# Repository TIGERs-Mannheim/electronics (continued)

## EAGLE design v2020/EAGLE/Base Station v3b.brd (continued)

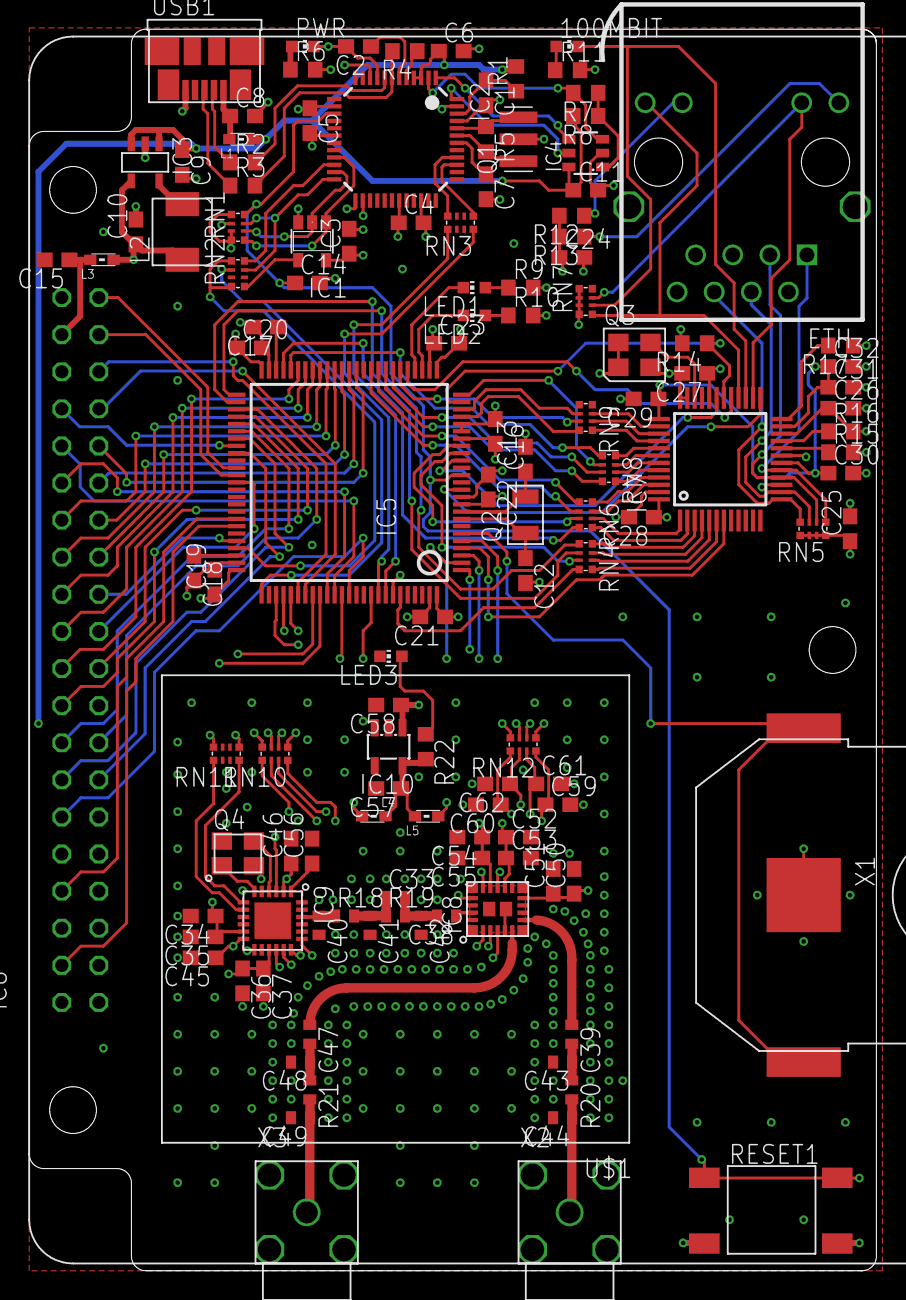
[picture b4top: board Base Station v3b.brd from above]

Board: 4 copper layers, 58.0 x 85.0 mm, 127 parts (0 on the bottom side), 157 nets.

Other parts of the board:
U$1: BMI-S-204-F; SHIELD-32MM

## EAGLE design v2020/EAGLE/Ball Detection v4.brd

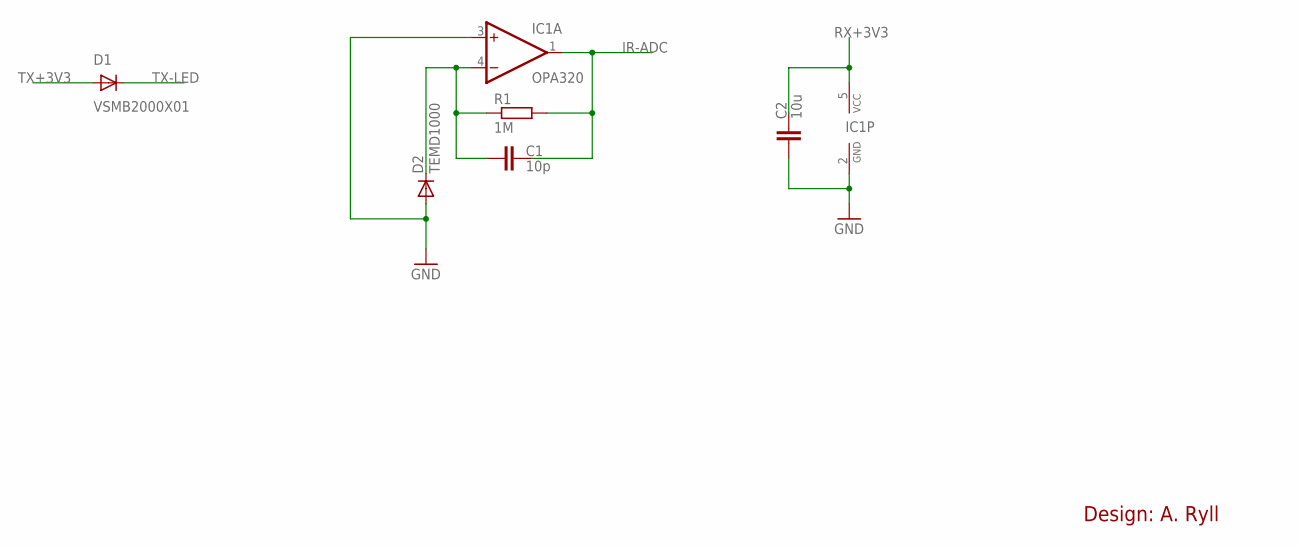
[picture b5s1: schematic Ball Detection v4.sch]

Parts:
C1: 10p; C0603
C2: 10u; C0603
D1: VSMB2000X01; LED-GULLR
D2: TEMD1000; LED-GULLR
IC1: OPA320; SOT23-5
R1: 1M; R0603

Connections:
GND: C2.1, D2.A, IC1.2 (GND), IC1.3 (+IN)
IR-ADC: C1.2, IC1.1 (OUT), R1.2
unnamed: C1.1, D2.C, IC1.4 (-IN), R1.1
RX+3V3: C2.2, IC1.5 (VCC)
TX+3V3: D1.A
TX-LED: D1.C

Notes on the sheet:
Design: A. Ryll

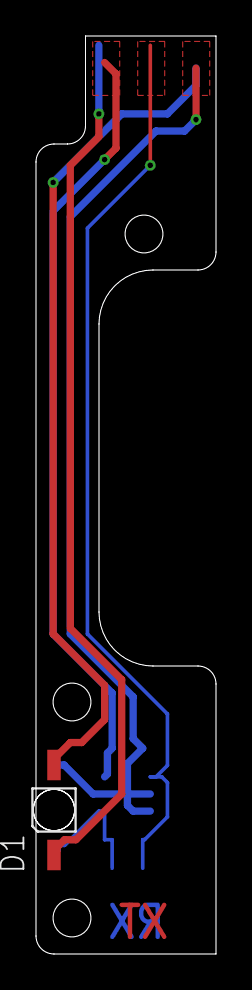
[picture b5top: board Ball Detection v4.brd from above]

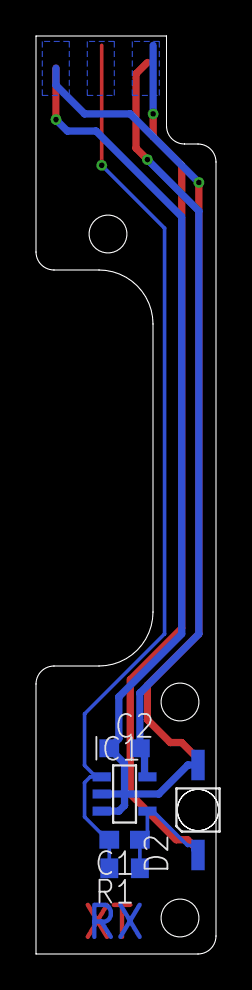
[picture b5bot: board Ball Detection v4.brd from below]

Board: 2 copper layers, 10.0 x 51.0 mm, 6 parts (5 on the bottom side), 4 nets.

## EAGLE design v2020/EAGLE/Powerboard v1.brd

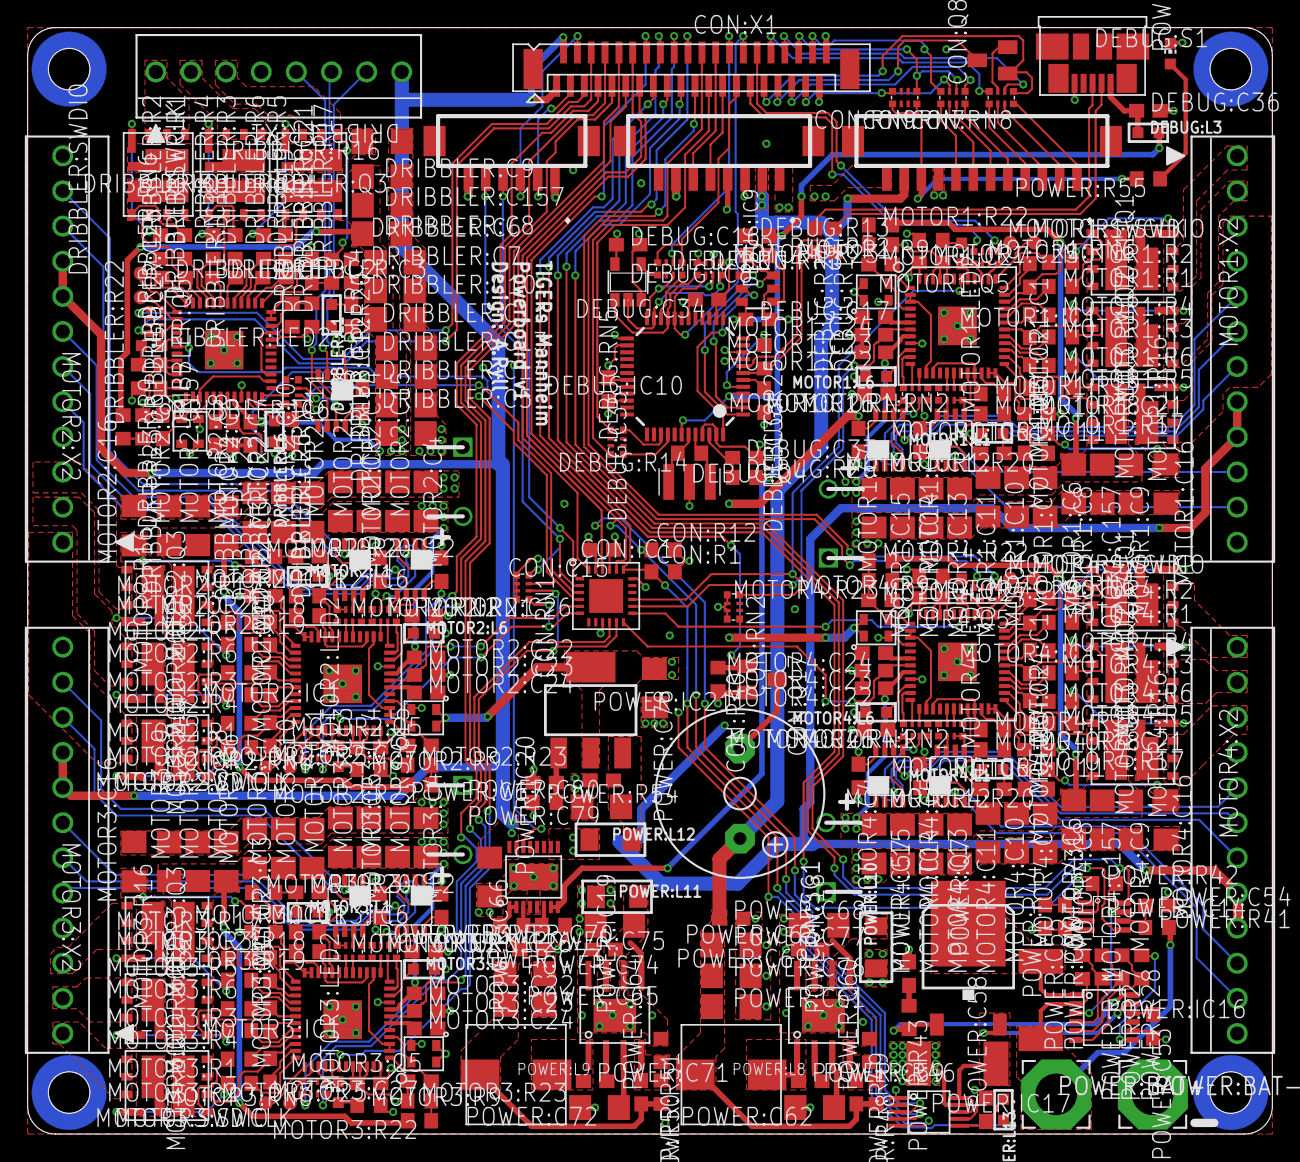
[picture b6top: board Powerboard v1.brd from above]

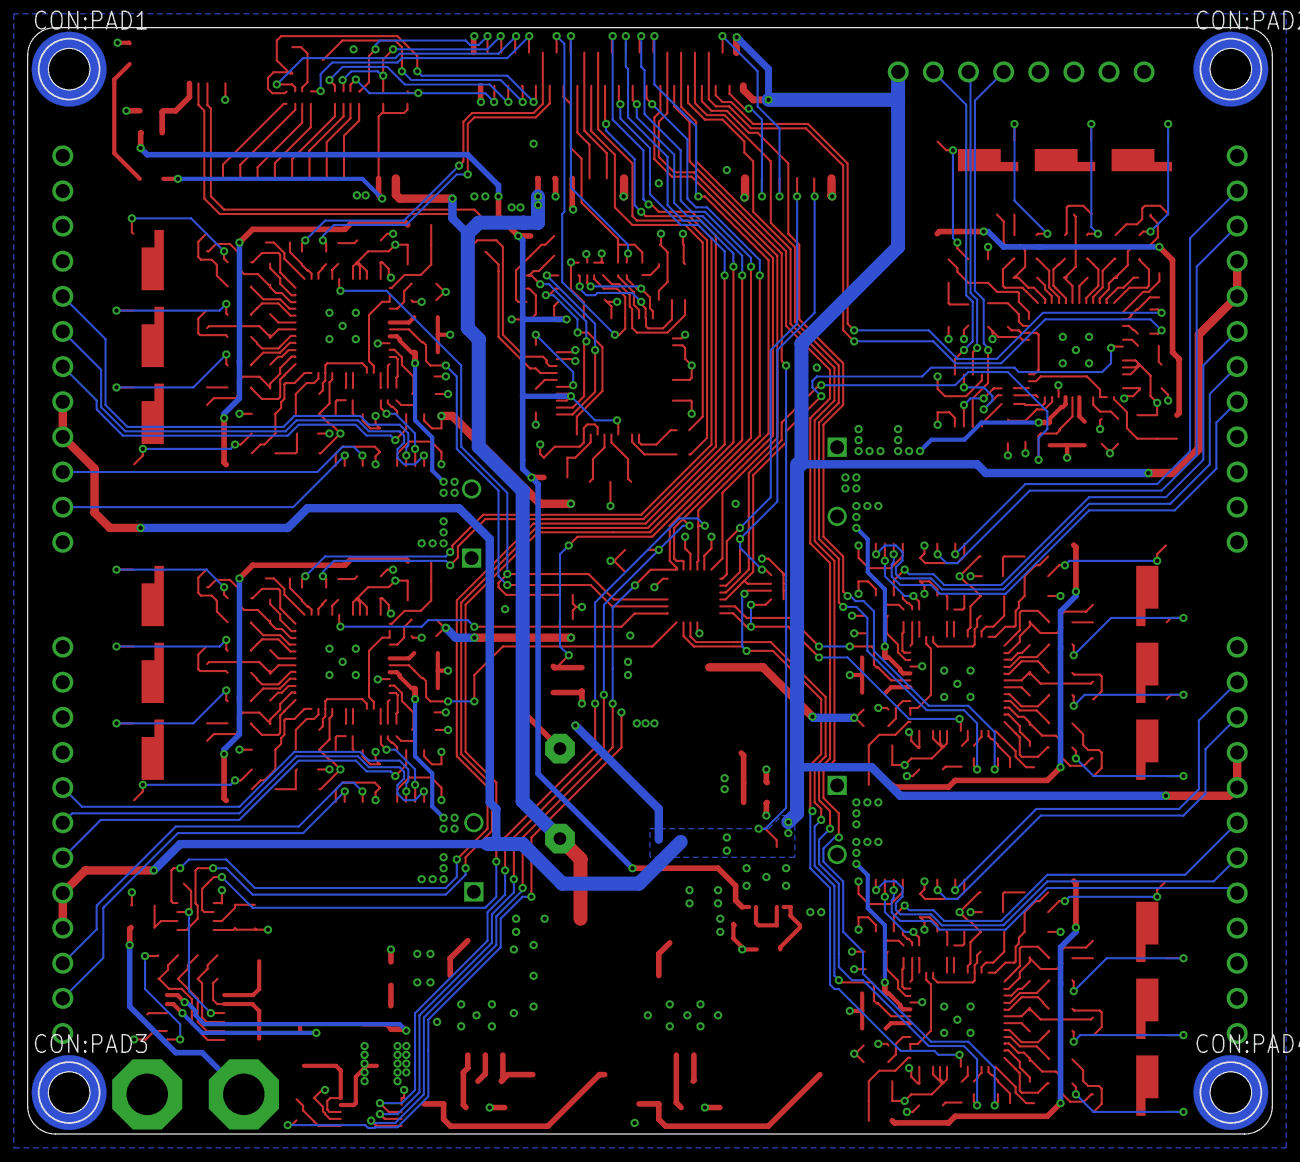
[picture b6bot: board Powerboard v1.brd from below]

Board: 4 copper layers, 90.0 x 80.0 mm, 372 parts (4 on the bottom side), 363 nets.

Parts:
CON:C15: 100n; C0603
CON:EXT: DF13-8P-1.25V; DF13C-8P-1.25V
CON:IC1: TCA9539RTW; WQFN24
CON:IR: DF13-6P-1.25V; DF13C-6P-1.25V
CON:KD: DF13-12P-1.25V; DF13C-12P-1.25V
CON:PAD1, CON:PAD2, CON:PAD3: 5,4/3,0
CON:PAD4: 9774030243R; 5,4/3,0
CON:Q8: BSS84; SOT23
CON:Q17: BSS138; SOT23
CON:R1, CON:R12: 1k33 1%; R0603
CON:R40: 5k6; R0603
CON:RN1, CON:RN2, CON:RN9: 10k; EXB28V
CON:RN7, CON:RN8: 100; EXB28V
CON:SG1: CEM-1212S; F/QMX
CON:X1: 4-1734742-0; TE-4-1734742-0
DEBUG:C16, DEBUG:C17, DEBUG:C34, DEBUG:C35, DEBUG:C36, DEBUG:C37, DEBUG:C38: 100n; C0603
DEBUG:IC8: 74LVC1G125DBV; SOT23-5
DEBUG:IC9: 93C76B; SOT23-6
DEBUG:IC10: FT2232ST; LQFP48-ST
DEBUG:L3: 120R; L0603
DEBUG:Q4: CSTCR6M00G55-R0; CSTCR6M
DEBUG:R12, DEBUG:R26: 1k; R0603
DEBUG:R13: 5k6; R0603
DEBUG:R14: 1M; R0603
DEBUG:R15, DEBUG:R24: 33; R0603
DEBUG:R25: 1k33 1%; R0603
DEBUG:RN3: 10k; EXB28V
DEBUG:RN4, DEBUG:RN5: 100; EXB28V
DEBUG:S1: USB-BU; USB-BMICRO
DRIBBLER:C1, DRIBBLER:C2, DRIBBLER:C3, DRIBBLER:C4, DRIBBLER:C12, DRIBBLER:C23, DRIBBLER:C25, DRIBBLER:C26: 100n; C0603
DRIBBLER:C5, DRIBBLER:C6, DRIBBLER:C7, DRIBBLER:C8, DRIBBLER:C9, DRIBBLER:C10, DRIBBLER:C11, DRIBBLER:C13, DRIBBLER:C14, DRIBBLER:C157: 10u; C1206
DRIBBLER:C21: 47p; C0603
DRIBBLER:C22, DRIBBLER:C24, DRIBBLER:C27: 1u; C0603
DRIBBLER:IC1: STSPIN32F0A; VFQFPN48
DRIBBLER:IC6: SN74LVC3G17DCT; DCT_R-PDSO-G8
DRIBBLER:L1, DRIBBLER:L6: 120R; L0603
DRIBBLER:LED2: gr; CHIP-LED0603
DRIBBLER:Q1, DRIBBLER:Q2, DRIBBLER:Q3: FDMD85100; POWER56_HBRIDGE
DRIBBLER:Q5: KC2016K4.00000C1GE00; OSCI-KC2016
DRIBBLER:R1, DRIBBLER:R2, DRIBBLER:R3, DRIBBLER:R4, DRIBBLER:R5, DRIBBLER:R6: 33; R0603
DRIBBLER:R9: 1k; R0603
DRIBBLER:R16: 0R025; R1206
DRIBBLER:R17, DRIBBLER:R18: 1k33 1%; R0603
DRIBBLER:R19: 7k32 1%; R0603
DRIBBLER:R20: 16k2 1%; R0603
DRIBBLER:R22: 243k 1%; R0603
DRIBBLER:R23: 24k 1%; R0603
DRIBBLER:RN1, DRIBBLER:RN6: 100; EXB28V
DRIBBLER:SWCLK: TPTP10R; TP10R
DRIBBLER:SWDIO: TPTP10R; TP10R
DRIBBLER:X1: 640454-8
MOTOR1:C1, MOTOR1:C2, MOTOR1:C3, MOTOR1:C4, MOTOR1:C5, MOTOR1:C12, MOTOR1:C23, MOTOR1:C25, MOTOR1:C26, MOTOR2:C1, MOTOR2:C2, MOTOR2:C3, MOTOR2:C4, MOTOR2:C5, MOTOR2:C12, MOTOR2:C23, MOTOR2:C25, MOTOR2:C26, MOTOR3:C1, MOTOR3:C2, MOTOR3:C3, MOTOR3:C4, MOTOR3:C5, MOTOR3:C12, MOTOR3:C23, MOTOR3:C25, MOTOR3:C26, MOTOR4:C1, MOTOR4:C2, MOTOR4:C3, MOTOR4:C4, MOTOR4:C5, MOTOR4:C12, MOTOR4:C23, MOTOR4:C25, MOTOR4:C26: 100n; C0603
MOTOR1:C6, MOTOR1:C7, MOTOR1:C8, MOTOR1:C9, MOTOR1:C10, MOTOR1:C11, MOTOR1:C13, MOTOR1:C14, MOTOR1:C15, MOTOR1:C157, MOTOR2:C6, MOTOR2:C7, MOTOR2:C8, MOTOR2:C9, MOTOR2:C10, MOTOR2:C11, MOTOR2:C13, MOTOR2:C14, MOTOR2:C15, MOTOR2:C157, MOTOR3:C6, MOTOR3:C7, MOTOR3:C8, MOTOR3:C9, MOTOR3:C10, MOTOR3:C11, MOTOR3:C13, MOTOR3:C14, MOTOR3:C15, MOTOR3:C157, MOTOR4:C6, MOTOR4:C7, MOTOR4:C8, MOTOR4:C9, MOTOR4:C10, MOTOR4:C11, MOTOR4:C13, MOTOR4:C14, MOTOR4:C15, MOTOR4:C157: 10u; C1206
MOTOR1:C16, MOTOR2:C16, MOTOR3:C16, MOTOR4:C16: 470u; C22-12.5L
MOTOR1:C21, MOTOR2:C21, MOTOR3:C21, MOTOR4:C21: 47p; C0603
MOTOR1:C22, MOTOR1:C24, MOTOR1:C27, MOTOR2:C22, MOTOR2:C24, MOTOR2:C27, MOTOR3:C22, MOTOR3:C24, MOTOR3:C27, MOTOR4:C22, MOTOR4:C24, MOTOR4:C27: 1u; C0603
MOTOR1:IC1, MOTOR2:IC1, MOTOR3:IC1, MOTOR4:IC1: STSPIN32F0A; VFQFPN48
MOTOR1:IC6, MOTOR1:IC11, MOTOR2:IC6, MOTOR2:IC11, MOTOR3:IC6, MOTOR3:IC11, MOTOR4:IC6, MOTOR4:IC11: SN74LVC3G17DCT; DCT_R-PDSO-G8
MOTOR1:L1, MOTOR1:L6, MOTOR2:L1, MOTOR2:L6, MOTOR3:L1, MOTOR3:L6, MOTOR4:L1, MOTOR4:L6: 120R; L0603
MOTOR1:LED2, MOTOR2:LED2, MOTOR3:LED2, MOTOR4:LED2: gr; CHIP-LED0603
MOTOR1:Q1, MOTOR1:Q2, MOTOR1:Q3, MOTOR2:Q1, MOTOR2:Q2, MOTOR2:Q3, MOTOR3:Q1, MOTOR3:Q2, MOTOR3:Q3, MOTOR4:Q1, MOTOR4:Q2, MOTOR4:Q3: FDMD85100; POWER56_HBRIDGE
MOTOR1:Q5, MOTOR2:Q5, MOTOR3:Q5, MOTOR4:Q5: KC2016K4.00000C1GE00; OSCI-KC2016
MOTOR1:R1, MOTOR1:R2, MOTOR1:R3, MOTOR1:R4, MOTOR1:R5, MOTOR1:R6, MOTOR2:R1, MOTOR2:R2, MOTOR2:R3, MOTOR2:R4, MOTOR2:R5, MOTOR2:R6, MOTOR3:R1, MOTOR3:R2, MOTOR3:R3, MOTOR3:R4, MOTOR3:R5, MOTOR3:R6, MOTOR4:R1, MOTOR4:R2, MOTOR4:R3, MOTOR4:R4, MOTOR4:R5, MOTOR4:R6: 33; R0603
MOTOR1:R9, MOTOR2:R9, MOTOR3:R9, MOTOR4:R9: 1k; R0603
MOTOR1:R16, MOTOR2:R16, MOTOR3:R16, MOTOR4:R16: 0R025; R1206
MOTOR1:R17, MOTOR1:R18, MOTOR2:R17, MOTOR2:R18, MOTOR3:R17, MOTOR3:R18, MOTOR4:R17, MOTOR4:R18: 1k33 1%; R0603
MOTOR1:R19, MOTOR2:R19, MOTOR3:R19, MOTOR4:R19: 7k32 1%; R0603
MOTOR1:R20, MOTOR2:R20, MOTOR3:R20, MOTOR4:R20: 16k2 1%; R0603
MOTOR1:R22, MOTOR2:R22, MOTOR3:R22, MOTOR4:R22: 243k 1%; R0603
MOTOR1:R23, MOTOR2:R23, MOTOR3:R23, MOTOR4:R23: 24k 1%; R0603
MOTOR1:RN1, MOTOR1:RN2, MOTOR1:RN6, MOTOR2:RN1, MOTOR2:RN2, MOTOR2:RN6, MOTOR3:RN1, MOTOR3:RN2, MOTOR3:RN6, MOTOR4:RN1, MOTOR4:RN2, MOTOR4:RN6: 100; EXB28V
MOTOR1:SWCLK, MOTOR1:SWDIO, MOTOR2:SWCLK, MOTOR2:SWDIO, MOTOR3:SWCLK, MOTOR3:SWDIO, MOTOR4:SWCLK, MOTOR4:SWDIO: TPTP10R; TP10R
MOTOR1:X2, MOTOR2:X2, MOTOR3:X2, MOTOR4:X2: 1-640454-2
POWER:BAT+: 5,08/3
POWER:BAT-: 5,08/3
POWER:C53, POWER:C54, POWER:C55, POWER:C56, POWER:C58, POWER:C67, POWER:C68, POWER:C69, POWER:C73, POWER:C75, POWER:C80: 100n; C0603
POWER:C57: 10n; C0603
POWER:C59, POWER:C71: 1u; C0603
POWER:C60, POWER:C64: 18p; C0603
POWER:C61, POWER:C65, POWER:C74, POWER:C76, POWER:C77, POWER:C78, POWER:C79: 33u; C1206
POWER:C62, POWER:C63, POWER:C66, POWER:C70, POWER:C72: 10u; C1206
POWER:IC14: LTC2955CTS8-1; SOT23-8
POWER:IC16: LTC4231CMS-2; MSOP-12
POWER:IC17: INA226; DGS_S-PDSO-G10
POWER:IC18, POWER:IC19: LMR23630ADDA; DDA_R-PDSO-G8
POWER:IC20: LTC4415MSE; MSOP-16P
POWER:IC21: LT3080ST; SOT223
POWER:L8, POWER:L9: 7443251600; WE-HCI
POWER:L10, POWER:L11, POWER:L12: 470R; L1206
POWER:L13: 120R; L0603
POWER:LED1: gr; CHIP-LED0603
POWER:Q7: FDD86367; D-PAK_TO252AA
POWER:R11: 5k6; R0603
POWER:R27: 40k2 1%; R0603
POWER:R28: 24k 1%; R0603
POWER:R31, POWER:R42: 1M; R0603
POWER:R41: 7k32 1%; R0603
POWER:R43, POWER:R55: 1k; R0603
POWER:R44: 0R001; R2512
POWER:R46: 0R002; R2512
POWER:R48: 243k 1%; R0603
POWER:R49, POWER:R51, POWER:R52: 22k1 1%; R0603
POWER:R50, POWER:R53: 88k7 1%; R0603
POWER:R54: 330k; R0603

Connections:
5V_USB: DEBUG:C17.1, DEBUG:IC9.6, DEBUG:IC10.3, DEBUG:IC10.4, DEBUG:IC10.42, DEBUG:L3.2, DEBUG:R13.2, DEBUG:R26.2, POWER:IC20.7, POWER:IC20.8
+3V3: CON:C15.1, CON:EXT.P$4, CON:IC1.21, CON:IR.P$1, CON:KD.P$10, CON:R1.2, CON:R12.2, CON:RN9.5, CON:RN9.8, DEBUG:C16.1, DEBUG:C34.1, DEBUG:C35.1, DEBUG:IC8.5, DEBUG:IC10.10, DEBUG:IC10.14, DEBUG:IC10.26, DEBUG:IC10.31, DEBUG:RN3.5, DEBUG:RN3.7, DEBUG:RN3.8, DRIBBLER:C4.1, DRIBBLER:C25.1, DRIBBLER:IC1.9, DRIBBLER:IC1.48, DRIBBLER:IC6.8, DRIBBLER:L1.2, DRIBBLER:L6.2, DRIBBLER:Q5.1, DRIBBLER:Q5.4, DRIBBLER:R9.2, MOTOR1:C4.1, MOTOR1:C5.1, MOTOR1:C25.1, MOTOR1:IC1.9, MOTOR1:IC1.48, MOTOR1:IC6.8, MOTOR1:IC11.8, MOTOR1:L1.2, MOTOR1:L6.2, MOTOR1:Q5.1, MOTOR1:Q5.4, MOTOR1:R9.2, MOTOR2:C4.1, MOTOR2:C5.1, MOTOR2:C25.1, MOTOR2:IC1.9, MOTOR2:IC1.48, MOTOR2:IC6.8, MOTOR2:IC11.8, MOTOR2:L1.2, MOTOR2:L6.2, MOTOR2:Q5.1, MOTOR2:Q5.4, MOTOR2:R9.2, MOTOR3:C4.1, MOTOR3:C5.1, MOTOR3:C25.1, MOTOR3:IC1.9, MOTOR3:IC1.48, MOTOR3:IC6.8, MOTOR3:IC11.8, MOTOR3:L1.2, MOTOR3:L6.2, MOTOR3:Q5.1, MOTOR3:Q5.4, MOTOR3:R9.2, MOTOR4:C4.1, MOTOR4:C5.1, MOTOR4:C25.1, MOTOR4:IC1.9, MOTOR4:IC1.48, MOTOR4:IC6.8, MOTOR4:IC11.8, MOTOR4:L1.2, MOTOR4:L6.2, MOTOR4:Q5.1, MOTOR4:Q5.4, MOTOR4:R9.2, POWER:C78.1, POWER:IC21.2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
+5V: CON:EXT.P$3, CON:X1.1, CON:X1.2, DRIBBLER:X1.8, MOTOR1:X2.8, MOTOR1:X2.9, MOTOR2:X2.8, MOTOR2:X2.9, MOTOR3:X2.8, MOTOR3:X2.9, MOTOR4:X2.8, MOTOR4:X2.9, POWER:C66.1, POWER:IC20.9, POWER:IC20.10, POWER:IC20.15, POWER:IC20.16, POWER:L12.1
+12V: CON:EXT.P$2, CON:KD.P$11, CON:SG1.+, POWER:C60.1, POWER:C61.1, POWER:C68.1, POWER:C76.1, POWER:C77.1, POWER:L8.1, POWER:R48.2
BOOT0: CON:IC1.15, CON:RN2.8, MOTOR1:IC1.42
BOOT1: CON:IC1.6, CON:RN1.5, MOTOR2:IC1.42
BOOT2: CON:IC1.11, CON:RN1.6, MOTOR3:IC1.42
BOOT3: CON:IC1.13, CON:RN2.5, MOTOR4:IC1.42
BOOT4: CON:IC1.4, CON:RN1.7, DRIBBLER:IC1.42
BOOT5: CON:IC1.2, CON:IR.P$5, CON:RN1.8
BTN: CON:X1.18, POWER:IC14.5
CON:BUZZER: CON:Q17.1, CON:R40.1, CON:X1.16
CON:KICK-CHG: CON:RN7.1, CON:X1.35
CON:KICK-CLK: CON:RN8.2, CON:X1.34
CON:KICK-CS: CON:Q8.1, CON:RN8.1, CON:X1.31
CON:KICK-DIS1: CON:RN7.2, CON:RN9.1, CON:X1.36
CON:KICK-DIS2: CON:RN7.3, CON:RN9.4, CON:X1.37
CON:KICK-ERR: CON:RN7.4, CON:X1.38
CON:KICK-MISO: CON:Q8.3, CON:X1.33
CON:KICK-MOSI: CON:RN8.4, CON:X1.32
CON:N$1: CON:Q17.3, CON:SG1.-
CON:N$2: CON:Q8.2, CON:RN8.3
CON:N$3: CON:KD.P$1, CON:RN8.8
CON:N$4: CON:KD.P$2, CON:RN8.7
CON:N$5: CON:KD.P$3, CON:RN8.6
CON:N$6: CON:KD.P$4, CON:RN8.5
CON:N$7: CON:KD.P$5, CON:RN7.8
CON:N$8: CON:KD.P$6, CON:RN7.7
CON:N$9: CON:KD.P$7, CON:RN7.6
CON:N$10: CON:KD.P$8, CON:RN7.5
CON:SMB-RST: CON:IC1.24, CON:X1.12
DEBUG:EECS: DEBUG:IC9.5, DEBUG:IC10.48
DEBUG:EEDATA: DEBUG:IC9.3, DEBUG:IC10.2, DEBUG:R12.1
DEBUG:EESK: DEBUG:IC9.4, DEBUG:IC10.1
DEBUG:N$61: DEBUG:IC9.1, DEBUG:R12.2, DEBUG:R13.1
DEBUG:N$62: DEBUG:IC10.43, DEBUG:Q4.1, DEBUG:R14.2
DEBUG:N$63: DEBUG:IC10.40, DEBUG:RN5.1
DEBUG:N$64: DEBUG:IC10.44, DEBUG:Q4.3, DEBUG:R14.1
DEBUG:N$71: DEBUG:IC10.8, DEBUG:R15.2
DEBUG:N$72: DEBUG:IC10.7, DEBUG:R24.2, DEBUG:R25.2
DEBUG:N$85: DEBUG:R15.1, DEBUG:S1.2
DEBUG:N$86: DEBUG:R24.1, DEBUG:S1.3
DEBUG:N$87: DEBUG:IC10.5, DEBUG:R25.1
DEBUG:N$88: DEBUG:C37.1, DEBUG:IC10.46, DEBUG:R26.1
DEBUG:N$89: DEBUG:IC10.24, DEBUG:RN3.3, DEBUG:RN4.3
DEBUG:N$90: DEBUG:C36.1, DEBUG:L3.1, DEBUG:S1.1
DEBUG:N$91: DEBUG:IC8.2, DEBUG:IC10.23, DEBUG:RN3.4
DEBUG:N$92: DEBUG:IC8.4, DEBUG:RN4.1
DEBUG:N$93: DEBUG:IC10.39, DEBUG:RN5.4
DEBUG:N$94: DEBUG:IC10.22, DEBUG:RN4.4
DEBUG:N$95: DEBUG:IC8.1, DEBUG:IC10.21, DEBUG:RN3.1
DEBUG:N$96: DEBUG:C38.1, DEBUG:IC10.6
DRIBBLER:M1-CUR: DRIBBLER:IC1.15, DRIBBLER:IC1.21, DRIBBLER:R19.1
DRIBBLER:M1-H1: DRIBBLER:IC6.3, DRIBBLER:X1.6
DRIBBLER:M1-H2: DRIBBLER:IC6.6, DRIBBLER:X1.5
DRIBBLER:M1-H3: DRIBBLER:IC6.1, DRIBBLER:X1.7
DRIBBLER:M1-LED: DRIBBLER:IC1.41, DRIBBLER:LED2.C
DRIBBLER:M1-TIM2-CH1: DRIBBLER:IC1.11, DRIBBLER:RN1.4
DRIBBLER:M1-TIM2-CH2: DRIBBLER:IC1.12, DRIBBLER:RN1.3
DRIBBLER:M1-TIM2-CH3: DRIBBLER:IC1.13, DRIBBLER:RN1.2
DRIBBLER:M1-VOL: DRIBBLER:IC1.2, DRIBBLER:IC1.3, DRIBBLER:IC1.14
DRIBBLER:MGND: DRIBBLER:Q1.S2, DRIBBLER:Q2.S2, DRIBBLER:Q3.S2, DRIBBLER:R16.2, DRIBBLER:R17.2
DRIBBLER:N$1: DRIBBLER:C1.2, DRIBBLER:IC1.34, DRIBBLER:Q1.2
DRIBBLER:N$2: DRIBBLER:C3.2, DRIBBLER:IC1.26, DRIBBLER:Q3.2
DRIBBLER:N$3: DRIBBLER:C2.2, DRIBBLER:IC1.30, DRIBBLER:Q2.2
DRIBBLER:N$4: DRIBBLER:Q2.1, DRIBBLER:R3.2
DRIBBLER:N$5: DRIBBLER:Q2.8, DRIBBLER:R4.2
DRIBBLER:N$6: DRIBBLER:Q3.1, DRIBBLER:R5.2
DRIBBLER:N$7: DRIBBLER:Q3.8, DRIBBLER:R6.2
DRIBBLER:N$8: DRIBBLER:Q1.8, DRIBBLER:R2.2
DRIBBLER:N$9: DRIBBLER:Q1.1, DRIBBLER:R1.2
DRIBBLER:N$10: DRIBBLER:IC1.33, DRIBBLER:R1.1
DRIBBLER:N$11: DRIBBLER:IC1.36, DRIBBLER:R2.1
DRIBBLER:N$12: DRIBBLER:IC1.29, DRIBBLER:R3.1
DRIBBLER:N$13: DRIBBLER:IC1.32, DRIBBLER:R4.1
DRIBBLER:N$14: DRIBBLER:IC1.25, DRIBBLER:R5.1
DRIBBLER:N$15: DRIBBLER:IC1.28, DRIBBLER:R6.1
DRIBBLER:N$16: DRIBBLER:C1.1, DRIBBLER:IC1.35
DRIBBLER:N$17: DRIBBLER:C2.1, DRIBBLER:IC1.31
DRIBBLER:N$18: DRIBBLER:C3.1, DRIBBLER:IC1.27
DRIBBLER:N$19: DRIBBLER:Q1.5, DRIBBLER:Q1.6, DRIBBLER:Q1.7, DRIBBLER:X1.1
DRIBBLER:N$20: DRIBBLER:Q2.5, DRIBBLER:Q2.6, DRIBBLER:Q2.7, DRIBBLER:X1.2
DRIBBLER:N$21: DRIBBLER:Q3.5, DRIBBLER:Q3.6, DRIBBLER:Q3.7, DRIBBLER:X1.3
DRIBBLER:N$23: DRIBBLER:IC6.5, DRIBBLER:RN1.5
DRIBBLER:N$24: DRIBBLER:IC6.2, DRIBBLER:RN1.6
DRIBBLER:N$25: DRIBBLER:IC6.7, DRIBBLER:RN1.7
DRIBBLER:N$27: DRIBBLER:C12.1, DRIBBLER:L1.1, DRIBBLER:R20.2
DRIBBLER:N$29: DRIBBLER:LED2.A, DRIBBLER:R9.1
DRIBBLER:N$31: DRIBBLER:IC1.39, DRIBBLER:RN6.1
DRIBBLER:N$35: DRIBBLER:C26.1, DRIBBLER:IC1.10, DRIBBLER:L6.1
DRIBBLER:N$39: DRIBBLER:IC1.22, DRIBBLER:R18.2, DRIBBLER:R19.2
DRIBBLER:N$40: DRIBBLER:C21.1, DRIBBLER:IC1.23, DRIBBLER:IC1.24, DRIBBLER:R17.1, DRIBBLER:R20.1
DRIBBLER:N$43: DRIBBLER:C24.1, DRIBBLER:IC1.6
DRIBBLER:N$45: DRIBBLER:C27.1, DRIBBLER:IC1.1, DRIBBLER:R22.1, DRIBBLER:R23.2
DRIBBLER:N$47: DRIBBLER:IC1.4, DRIBBLER:Q5.3
DRIBBLER:SWCLK: DRIBBLER:IC1.38, DRIBBLER:RN6.4, DRIBBLER:SWCLK.TP
DRIBBLER:SWDIO: DRIBBLER:IC1.37, DRIBBLER:SWDIO.TP
GND: CON:C15.2, CON:EXT.P$7, CON:IC1.9, CON:IC1.18, CON:IC1.23, CON:IR.P$6, CON:KD.P$9, CON:PAD1.1, CON:PAD1.2, CON:PAD2.1, CON:PAD2.2, CON:PAD3.1, CON:PAD3.2, CON:PAD4.1, CON:PAD4.2, CON:Q17.2, CON:R40.2, CON:RN1.1, CON:RN1.2, CON:RN1.3, CON:RN1.4, CON:RN2.1, CON:RN2.2, CON:RN2.3, CON:RN2.4, CON:X1.39, CON:X1.40, DEBUG:C16.2, DEBUG:C17.2, DEBUG:C34.2, DEBUG:C35.2, DEBUG:C36.2, DEBUG:C37.2, DEBUG:C38.2, DEBUG:IC8.3, DEBUG:IC9.2, DEBUG:IC10.9, DEBUG:IC10.18, DEBUG:IC10.25, DEBUG:IC10.34, DEBUG:IC10.45, DEBUG:IC10.47, DEBUG:Q4.2, DEBUG:RN3.6, DEBUG:S1.5, DRIBBLER:C4.2, DRIBBLER:C5.2, DRIBBLER:C6.2, DRIBBLER:C7.2, DRIBBLER:C8.2, DRIBBLER:C9.2, DRIBBLER:C10.2, DRIBBLER:C11.2, DRIBBLER:C12.2, DRIBBLER:C13.2, DRIBBLER:C14.2, DRIBBLER:C21.2, DRIBBLER:C22.2, DRIBBLER:C23.2, DRIBBLER:C24.2, DRIBBLER:C25.2, DRIBBLER:C26.2, DRIBBLER:C27.2, DRIBBLER:C157.2, DRIBBLER:IC1.20, DRIBBLER:IC1.44, DRIBBLER:IC1.45, DRIBBLER:IC1.46, DRIBBLER:IC1.PAD, DRIBBLER:IC6.4, DRIBBLER:Q5.2, DRIBBLER:R16.1, DRIBBLER:R18.1, DRIBBLER:R23.1, DRIBBLER:X1.4, MOTOR1:C4.2, MOTOR1:C5.2, MOTOR1:C6.2, MOTOR1:C7.2, MOTOR1:C8.2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
KILL: CON:X1.17, POWER:IC14.2, POWER:R42.1
MOTOR1:M1-CUR: MOTOR1:IC1.15, MOTOR1:IC1.21, MOTOR1:R19.1
MOTOR1:M1-ENCA: MOTOR1:IC11.1, MOTOR1:X2.10
MOTOR1:M1-ENCB: MOTOR1:IC11.3, MOTOR1:X2.11
MOTOR1:M1-H1: MOTOR1:IC6.1, MOTOR1:X2.6
MOTOR1:M1-H2: MOTOR1:IC6.3, MOTOR1:X2.5
MOTOR1:M1-H3: MOTOR1:IC6.6, MOTOR1:X2.7
MOTOR1:M1-LED: MOTOR1:IC1.41, MOTOR1:LED2.C
MOTOR1:M1-TIM2-CH1: MOTOR1:IC1.11, MOTOR1:RN1.4
MOTOR1:M1-TIM2-CH2: MOTOR1:IC1.12, MOTOR1:RN1.3
MOTOR1:M1-TIM2-CH3: MOTOR1:IC1.13, MOTOR1:RN1.2
MOTOR1:M1-TIM3-CH1: MOTOR1:IC1.17, MOTOR1:RN2.3
MOTOR1:M1-TIM3-CH2: MOTOR1:IC1.18, MOTOR1:RN2.2
MOTOR1:M1-VOL: MOTOR1:IC1.2, MOTOR1:IC1.3, MOTOR1:IC1.14
MOTOR1:MGND: MOTOR1:Q1.S2, MOTOR1:Q2.S2, MOTOR1:Q3.S2, MOTOR1:R16.2, MOTOR1:R17.2
MOTOR1:N$1: MOTOR1:C1.2, MOTOR1:IC1.34, MOTOR1:Q1.2
MOTOR1:N$2: MOTOR1:C3.2, MOTOR1:IC1.26, MOTOR1:Q3.2
MOTOR1:N$3: MOTOR1:C2.2, MOTOR1:IC1.30, MOTOR1:Q2.2
MOTOR1:N$4: MOTOR1:Q2.1, MOTOR1:R3.2
MOTOR1:N$5: MOTOR1:Q2.8, MOTOR1:R4.2
MOTOR1:N$6: MOTOR1:Q3.1, MOTOR1:R5.2
MOTOR1:N$7: MOTOR1:Q3.8, MOTOR1:R6.2
MOTOR1:N$8: MOTOR1:Q1.8, MOTOR1:R2.2
MOTOR1:N$9: MOTOR1:Q1.1, MOTOR1:R1.2
MOTOR1:N$10: MOTOR1:IC1.33, MOTOR1:R1.1
MOTOR1:N$11: MOTOR1:IC1.36, MOTOR1:R2.1
MOTOR1:N$12: MOTOR1:IC1.29, MOTOR1:R3.1
MOTOR1:N$13: MOTOR1:IC1.32, MOTOR1:R4.1
MOTOR1:N$14: MOTOR1:IC1.25, MOTOR1:R5.1
MOTOR1:N$15: MOTOR1:IC1.28, MOTOR1:R6.1
MOTOR1:N$16: MOTOR1:C1.1, MOTOR1:IC1.35
MOTOR1:N$17: MOTOR1:C2.1, MOTOR1:IC1.31
MOTOR1:N$18: MOTOR1:C3.1, MOTOR1:IC1.27
MOTOR1:N$22: MOTOR1:IC11.7, MOTOR1:RN2.6
MOTOR1:N$23: MOTOR1:IC6.7, MOTOR1:RN1.5
MOTOR1:N$24: MOTOR1:IC6.5, MOTOR1:RN1.6
MOTOR1:N$25: MOTOR1:IC6.2, MOTOR1:RN1.7
MOTOR1:N$26: MOTOR1:IC11.5, MOTOR1:RN2.7, MOTOR1:RN2.8
MOTOR1:N$27: MOTOR1:C12.1, MOTOR1:L1.1, MOTOR1:R20.2
MOTOR1:N$29: MOTOR1:LED2.A, MOTOR1:R9.1
MOTOR1:N$31: MOTOR1:IC1.39, MOTOR1:RN6.1
MOTOR1:N$35: MOTOR1:C26.1, MOTOR1:IC1.10, MOTOR1:L6.1
MOTOR1:N$39: MOTOR1:IC1.22, MOTOR1:R18.2, MOTOR1:R19.2
MOTOR1:N$40: MOTOR1:C21.1, MOTOR1:IC1.23, MOTOR1:IC1.24, MOTOR1:R17.1, MOTOR1:R20.1
MOTOR1:N$43: MOTOR1:C24.1, MOTOR1:IC1.6
MOTOR1:N$45: MOTOR1:C27.1, MOTOR1:IC1.1, MOTOR1:R22.1, MOTOR1:R23.2
MOTOR1:N$47: MOTOR1:IC1.4, MOTOR1:Q5.3
MOTOR1:SWDCLK: MOTOR1:IC1.38, MOTOR1:RN6.4, MOTOR1:SWCLK.TP
MOTOR1:SWDIO: MOTOR1:IC1.37, MOTOR1:SWDIO.TP
MOTOR1:WU: MOTOR1:Q1.5, MOTOR1:Q1.6, MOTOR1:Q1.7, MOTOR1:X2.1
MOTOR1:WV: MOTOR1:Q2.5, MOTOR1:Q2.6, MOTOR1:Q2.7, MOTOR1:X2.2
MOTOR1:WW: MOTOR1:Q3.5, MOTOR1:Q3.6, MOTOR1:Q3.7, MOTOR1:X2.3
MOTOR2:M1-CUR: MOTOR2:IC1.15, MOTOR2:IC1.21, MOTOR2:R19.1
MOTOR2:M1-ENCA: MOTOR2:IC11.1, MOTOR2:X2.10
MOTOR2:M1-ENCB: MOTOR2:IC11.3, MOTOR2:X2.11
MOTOR2:M1-H1: MOTOR2:IC6.1, MOTOR2:X2.6
MOTOR2:M1-H2: MOTOR2:IC6.3, MOTOR2:X2.5
MOTOR2:M1-H3: MOTOR2:IC6.6, MOTOR2:X2.7
MOTOR2:M1-LED: MOTOR2:IC1.41, MOTOR2:LED2.C
MOTOR2:M1-TIM2-CH1: MOTOR2:IC1.11, MOTOR2:RN1.4
MOTOR2:M1-TIM2-CH2: MOTOR2:IC1.12, MOTOR2:RN1.3
MOTOR2:M1-TIM2-CH3: MOTOR2:IC1.13, MOTOR2:RN1.2
MOTOR2:M1-TIM3-CH1: MOTOR2:IC1.17, MOTOR2:RN2.3
MOTOR2:M1-TIM3-CH2: MOTOR2:IC1.18, MOTOR2:RN2.2
MOTOR2:M1-VOL: MOTOR2:IC1.2, MOTOR2:IC1.3, MOTOR2:IC1.14
MOTOR2:MGND: MOTOR2:Q1.S2, MOTOR2:Q2.S2, MOTOR2:Q3.S2, MOTOR2:R16.2, MOTOR2:R17.2
MOTOR2:N$1: MOTOR2:C1.2, MOTOR2:IC1.34, MOTOR2:Q1.2
MOTOR2:N$2: MOTOR2:C3.2, MOTOR2:IC1.26, MOTOR2:Q3.2
MOTOR2:N$3: MOTOR2:C2.2, MOTOR2:IC1.30, MOTOR2:Q2.2
MOTOR2:N$4: MOTOR2:Q2.1, MOTOR2:R3.2
MOTOR2:N$5: MOTOR2:Q2.8, MOTOR2:R4.2
MOTOR2:N$6: MOTOR2:Q3.1, MOTOR2:R5.2
MOTOR2:N$7: MOTOR2:Q3.8, MOTOR2:R6.2
MOTOR2:N$8: MOTOR2:Q1.8, MOTOR2:R2.2
MOTOR2:N$9: MOTOR2:Q1.1, MOTOR2:R1.2
MOTOR2:N$10: MOTOR2:IC1.33, MOTOR2:R1.1
MOTOR2:N$11: MOTOR2:IC1.36, MOTOR2:R2.1
MOTOR2:N$12: MOTOR2:IC1.29, MOTOR2:R3.1
MOTOR2:N$13: MOTOR2:IC1.32, MOTOR2:R4.1
MOTOR2:N$14: MOTOR2:IC1.25, MOTOR2:R5.1
MOTOR2:N$15: MOTOR2:IC1.28, MOTOR2:R6.1
MOTOR2:N$16: MOTOR2:C1.1, MOTOR2:IC1.35
MOTOR2:N$17: MOTOR2:C2.1, MOTOR2:IC1.31
MOTOR2:N$18: MOTOR2:C3.1, MOTOR2:IC1.27
MOTOR2:N$22: MOTOR2:IC11.7, MOTOR2:RN2.6
MOTOR2:N$23: MOTOR2:IC6.7, MOTOR2:RN1.5
MOTOR2:N$24: MOTOR2:IC6.5, MOTOR2:RN1.6
MOTOR2:N$25: MOTOR2:IC6.2, MOTOR2:RN1.7
MOTOR2:N$26: MOTOR2:IC11.5, MOTOR2:RN2.7, MOTOR2:RN2.8
MOTOR2:N$27: MOTOR2:C12.1, MOTOR2:L1.1, MOTOR2:R20.2
MOTOR2:N$29: MOTOR2:LED2.A, MOTOR2:R9.1
MOTOR2:N$31: MOTOR2:IC1.39, MOTOR2:RN6.1
MOTOR2:N$35: MOTOR2:C26.1, MOTOR2:IC1.10, MOTOR2:L6.1
MOTOR2:N$39: MOTOR2:IC1.22, MOTOR2:R18.2, MOTOR2:R19.2
MOTOR2:N$40: MOTOR2:C21.1, MOTOR2:IC1.23, MOTOR2:IC1.24, MOTOR2:R17.1, MOTOR2:R20.1
MOTOR2:N$43: MOTOR2:C24.1, MOTOR2:IC1.6
MOTOR2:N$45: MOTOR2:C27.1, MOTOR2:IC1.1, MOTOR2:R22.1, MOTOR2:R23.2
MOTOR2:N$47: MOTOR2:IC1.4, MOTOR2:Q5.3
MOTOR2:SWDCLK: MOTOR2:IC1.38, MOTOR2:RN6.4, MOTOR2:SWCLK.TP
MOTOR2:SWDIO: MOTOR2:IC1.37, MOTOR2:SWDIO.TP
MOTOR2:WU: MOTOR2:Q1.5, MOTOR2:Q1.6, MOTOR2:Q1.7, MOTOR2:X2.1
MOTOR2:WV: MOTOR2:Q2.5, MOTOR2:Q2.6, MOTOR2:Q2.7, MOTOR2:X2.2
MOTOR2:WW: MOTOR2:Q3.5, MOTOR2:Q3.6, MOTOR2:Q3.7, MOTOR2:X2.3
MOTOR3:M1-CUR: MOTOR3:IC1.15, MOTOR3:IC1.21, MOTOR3:R19.1
MOTOR3:M1-ENCA: MOTOR3:IC11.1, MOTOR3:X2.10
MOTOR3:M1-ENCB: MOTOR3:IC11.3, MOTOR3:X2.11
MOTOR3:M1-H1: MOTOR3:IC6.1, MOTOR3:X2.6
MOTOR3:M1-H2: MOTOR3:IC6.3, MOTOR3:X2.5
MOTOR3:M1-H3: MOTOR3:IC6.6, MOTOR3:X2.7
MOTOR3:M1-LED: MOTOR3:IC1.41, MOTOR3:LED2.C
MOTOR3:M1-TIM2-CH1: MOTOR3:IC1.11, MOTOR3:RN1.4
MOTOR3:M1-TIM2-CH2: MOTOR3:IC1.12, MOTOR3:RN1.3
MOTOR3:M1-TIM2-CH3: MOTOR3:IC1.13, MOTOR3:RN1.2
MOTOR3:M1-TIM3-CH1: MOTOR3:IC1.17, MOTOR3:RN2.3
MOTOR3:M1-TIM3-CH2: MOTOR3:IC1.18, MOTOR3:RN2.2
MOTOR3:M1-VOL: MOTOR3:IC1.2, MOTOR3:IC1.3, MOTOR3:IC1.14
MOTOR3:MGND: MOTOR3:Q1.S2, MOTOR3:Q2.S2, MOTOR3:Q3.S2, MOTOR3:R16.2, MOTOR3:R17.2
MOTOR3:N$1: MOTOR3:C1.2, MOTOR3:IC1.34, MOTOR3:Q1.2
MOTOR3:N$2: MOTOR3:C3.2, MOTOR3:IC1.26, MOTOR3:Q3.2
MOTOR3:N$3: MOTOR3:C2.2, MOTOR3:IC1.30, MOTOR3:Q2.2
MOTOR3:N$4: MOTOR3:Q2.1, MOTOR3:R3.2
MOTOR3:N$5: MOTOR3:Q2.8, MOTOR3:R4.2
MOTOR3:N$6: MOTOR3:Q3.1, MOTOR3:R5.2
MOTOR3:N$7: MOTOR3:Q3.8, MOTOR3:R6.2
MOTOR3:N$8: MOTOR3:Q1.8, MOTOR3:R2.2
MOTOR3:N$9: MOTOR3:Q1.1, MOTOR3:R1.2
MOTOR3:N$10: MOTOR3:IC1.33, MOTOR3:R1.1
MOTOR3:N$11: MOTOR3:IC1.36, MOTOR3:R2.1
MOTOR3:N$12: MOTOR3:IC1.29, MOTOR3:R3.1
MOTOR3:N$13: MOTOR3:IC1.32, MOTOR3:R4.1
MOTOR3:N$14: MOTOR3:IC1.25, MOTOR3:R5.1
MOTOR3:N$15: MOTOR3:IC1.28, MOTOR3:R6.1
MOTOR3:N$16: MOTOR3:C1.1, MOTOR3:IC1.35
MOTOR3:N$17: MOTOR3:C2.1, MOTOR3:IC1.31
MOTOR3:N$18: MOTOR3:C3.1, MOTOR3:IC1.27
MOTOR3:N$22: MOTOR3:IC11.7, MOTOR3:RN2.6
MOTOR3:N$23: MOTOR3:IC6.7, MOTOR3:RN1.5
MOTOR3:N$24: MOTOR3:IC6.5, MOTOR3:RN1.6
MOTOR3:N$25: MOTOR3:IC6.2, MOTOR3:RN1.7
MOTOR3:N$26: MOTOR3:IC11.5, MOTOR3:RN2.7, MOTOR3:RN2.8
MOTOR3:N$27: MOTOR3:C12.1, MOTOR3:L1.1, MOTOR3:R20.2
MOTOR3:N$29: MOTOR3:LED2.A, MOTOR3:R9.1
MOTOR3:N$31: MOTOR3:IC1.39, MOTOR3:RN6.1
MOTOR3:N$35: MOTOR3:C26.1, MOTOR3:IC1.10, MOTOR3:L6.1
MOTOR3:N$39: MOTOR3:IC1.22, MOTOR3:R18.2, MOTOR3:R19.2
MOTOR3:N$40: MOTOR3:C21.1, MOTOR3:IC1.23, MOTOR3:IC1.24, MOTOR3:R17.1, MOTOR3:R20.1
MOTOR3:N$43: MOTOR3:C24.1, MOTOR3:IC1.6
MOTOR3:N$45: MOTOR3:C27.1, MOTOR3:IC1.1, MOTOR3:R22.1, MOTOR3:R23.2
MOTOR3:N$47: MOTOR3:IC1.4, MOTOR3:Q5.3
MOTOR3:SWDCLK: MOTOR3:IC1.38, MOTOR3:RN6.4, MOTOR3:SWCLK.TP
MOTOR3:SWDIO: MOTOR3:IC1.37, MOTOR3:SWDIO.TP
MOTOR3:WU: MOTOR3:Q1.5, MOTOR3:Q1.6, MOTOR3:Q1.7, MOTOR3:X2.1
MOTOR3:WV: MOTOR3:Q2.5, MOTOR3:Q2.6, MOTOR3:Q2.7, MOTOR3:X2.2
MOTOR3:WW: MOTOR3:Q3.5, MOTOR3:Q3.6, MOTOR3:Q3.7, MOTOR3:X2.3
MOTOR4:M1-CUR: MOTOR4:IC1.15, MOTOR4:IC1.21, MOTOR4:R19.1
MOTOR4:M1-ENCA: MOTOR4:IC11.1, MOTOR4:X2.10
MOTOR4:M1-ENCB: MOTOR4:IC11.3, MOTOR4:X2.11
MOTOR4:M1-H1: MOTOR4:IC6.1, MOTOR4:X2.6
MOTOR4:M1-H2: MOTOR4:IC6.3, MOTOR4:X2.5
MOTOR4:M1-H3: MOTOR4:IC6.6, MOTOR4:X2.7
MOTOR4:M1-LED: MOTOR4:IC1.41, MOTOR4:LED2.C
MOTOR4:M1-TIM2-CH1: MOTOR4:IC1.11, MOTOR4:RN1.4
MOTOR4:M1-TIM2-CH2: MOTOR4:IC1.12, MOTOR4:RN1.3
MOTOR4:M1-TIM2-CH3: MOTOR4:IC1.13, MOTOR4:RN1.2
MOTOR4:M1-TIM3-CH1: MOTOR4:IC1.17, MOTOR4:RN2.3
MOTOR4:M1-TIM3-CH2: MOTOR4:IC1.18, MOTOR4:RN2.2
MOTOR4:M1-VOL: MOTOR4:IC1.2, MOTOR4:IC1.3, MOTOR4:IC1.14
MOTOR4:MGND: MOTOR4:Q1.S2, MOTOR4:Q2.S2, MOTOR4:Q3.S2, MOTOR4:R16.2, MOTOR4:R17.2
MOTOR4:N$1: MOTOR4:C1.2, MOTOR4:IC1.34, MOTOR4:Q1.2
MOTOR4:N$2: MOTOR4:C3.2, MOTOR4:IC1.26, MOTOR4:Q3.2
MOTOR4:N$3: MOTOR4:C2.2, MOTOR4:IC1.30, MOTOR4:Q2.2
MOTOR4:N$4: MOTOR4:Q2.1, MOTOR4:R3.2
MOTOR4:N$5: MOTOR4:Q2.8, MOTOR4:R4.2
MOTOR4:N$6: MOTOR4:Q3.1, MOTOR4:R5.2
MOTOR4:N$7: MOTOR4:Q3.8, MOTOR4:R6.2
MOTOR4:N$8: MOTOR4:Q1.8, MOTOR4:R2.2
MOTOR4:N$9: MOTOR4:Q1.1, MOTOR4:R1.2
MOTOR4:N$10: MOTOR4:IC1.33, MOTOR4:R1.1
MOTOR4:N$11: MOTOR4:IC1.36, MOTOR4:R2.1
MOTOR4:N$12: MOTOR4:IC1.29, MOTOR4:R3.1
MOTOR4:N$13: MOTOR4:IC1.32, MOTOR4:R4.1
MOTOR4:N$14: MOTOR4:IC1.25, MOTOR4:R5.1
MOTOR4:N$15: MOTOR4:IC1.28, MOTOR4:R6.1
MOTOR4:N$16: MOTOR4:C1.1, MOTOR4:IC1.35
MOTOR4:N$17: MOTOR4:C2.1, MOTOR4:IC1.31
MOTOR4:N$18: MOTOR4:C3.1, MOTOR4:IC1.27
MOTOR4:N$22: MOTOR4:IC11.7, MOTOR4:RN2.6
MOTOR4:N$23: MOTOR4:IC6.7, MOTOR4:RN1.5
MOTOR4:N$24: MOTOR4:IC6.5, MOTOR4:RN1.6
MOTOR4:N$25: MOTOR4:IC6.2, MOTOR4:RN1.7
MOTOR4:N$26: MOTOR4:IC11.5, MOTOR4:RN2.7, MOTOR4:RN2.8
MOTOR4:N$27: MOTOR4:C12.1, MOTOR4:L1.1, MOTOR4:R20.2
MOTOR4:N$29: MOTOR4:LED2.A, MOTOR4:R9.1
MOTOR4:N$31: MOTOR4:IC1.39, MOTOR4:RN6.1
MOTOR4:N$35: MOTOR4:C26.1, MOTOR4:IC1.10, MOTOR4:L6.1
MOTOR4:N$39: MOTOR4:IC1.22, MOTOR4:R18.2, MOTOR4:R19.2
MOTOR4:N$40: MOTOR4:C21.1, MOTOR4:IC1.23, MOTOR4:IC1.24, MOTOR4:R17.1, MOTOR4:R20.1
MOTOR4:N$43: MOTOR4:C24.1, MOTOR4:IC1.6
MOTOR4:N$45: MOTOR4:C27.1, MOTOR4:IC1.1, MOTOR4:R22.1, MOTOR4:R23.2
MOTOR4:N$47: MOTOR4:IC1.4, MOTOR4:Q5.3
MOTOR4:SWDCLK: MOTOR4:IC1.38, MOTOR4:RN6.4, MOTOR4:SWCLK.TP
MOTOR4:SWDIO: MOTOR4:IC1.37, MOTOR4:SWDIO.TP
MOTOR4:WU: MOTOR4:Q1.5, MOTOR4:Q1.6, MOTOR4:Q1.7, MOTOR4:X2.1
MOTOR4:WV: MOTOR4:Q2.5, MOTOR4:Q2.6, MOTOR4:Q2.7, MOTOR4:X2.2
MOTOR4:WW: MOTOR4:Q3.5, MOTOR4:Q3.6, MOTOR4:Q3.7, MOTOR4:X2.3
PDN: CON:X1.19, POWER:IC14.8
POWER:5V_BAT: POWER:C64.1, POWER:C65.1, POWER:C74.1, POWER:C75.1, POWER:IC20.1, POWER:IC20.2, POWER:L9.1, POWER:R50.2, POWER:R53.2
POWER:N$33: POWER:C53.1, POWER:IC16.10
POWER:N$73: POWER:IC16.5, POWER:R11.1, POWER:R27.2
POWER:N$74: POWER:IC16.6, POWER:R27.1, POWER:R28.2
POWER:N$75: POWER:IC16.4, POWER:R11.2, POWER:R31.2
POWER:N$76: POWER:IC16.7, POWER:R28.1
POWER:N$77: POWER:C54.1, POWER:IC14.6, POWER:R41.1
POWER:N$79: POWER:C55.1, POWER:C56.1, POWER:IC14.3
POWER:N$80: POWER:IC14.7, POWER:IC16.3, POWER:R42.2
POWER:N$81: POWER:C57.1, POWER:R43.1
POWER:N$82: POWER:IC16.1, POWER:Q7.4, POWER:R44.2
POWER:N$83: POWER:IC16.12, POWER:Q7.1, POWER:R43.2
POWER:N$84: POWER:IC16.11, POWER:IC17.8, POWER:IC17.10, POWER:Q7.3, POWER:R46.1
POWER:N$98: POWER:C62.1, POWER:IC18.3
POWER:N$99: POWER:C59.1, POWER:IC18.1, POWER:L8.2
POWER:N$100: POWER:C60.2, POWER:IC18.4, POWER:R48.1, POWER:R49.2
POWER:N$101: POWER:C59.2, POWER:IC18.2
POWER:N$102: POWER:C72.1, POWER:IC19.3
POWER:N$103: POWER:C71.1, POWER:IC19.1, POWER:L9.2
POWER:N$104: POWER:C64.2, POWER:IC19.4, POWER:R50.1, POWER:R51.2
POWER:N$105: POWER:C71.2, POWER:IC19.2
POWER:N$106: POWER:IC20.3, POWER:IC20.6, POWER:R52.2, POWER:R53.1
POWER:N$107: POWER:C67.1, POWER:IC21.1, POWER:R54.2
POWER:N$108: POWER:LED1.A, POWER:R55.1
POWER:N$109: POWER:C63.1, POWER:C69.1, POWER:IC18.5, POWER:IC18.7, POWER:L10.2
POWER:N$110: POWER:C70.1, POWER:C73.1, POWER:IC19.5, POWER:IC19.7, POWER:L11.2
POWER:N$111: POWER:C79.1, POWER:C80.1, POWER:IC21.3, POWER:L12.2
POWER:N$112: POWER:C58.1, POWER:IC17.6, POWER:L13.1
POWER:V_BAT: POWER:BAT+.P$1, POWER:IC16.2, POWER:R31.1, POWER:R41.2, POWER:R44.1
RX0: CON:X1.30, MOTOR1:RN6.5
RX1: CON:X1.7, MOTOR2:RN6.5
RX2: CON:X1.9, MOTOR3:RN6.5
RX3: CON:X1.21, MOTOR4:RN6.5
RX4: CON:X1.5, DRIBBLER:RN6.5
RX5: CON:IR.P$2, CON:X1.3
RX6: CON:X1.23, DEBUG:RN5.5
RX7: CON:EXT.P$6, CON:X1.24
SMB-ALRT: CON:IC1.22, CON:X1.13, POWER:IC17.3
SMB-SCL: CON:IC1.19, CON:R1.1, CON:X1.15, POWER:IC17.5
SMB-SDA: CON:IC1.20, CON:R12.1, CON:X1.14, POWER:IC17.4
SRST: CON:X1.28, DEBUG:IC10.20, DEBUG:RN3.2
SRST0: CON:IC1.14, MOTOR1:C23.1, MOTOR1:IC1.7
SRST1: CON:IC1.5, MOTOR2:C23.1, MOTOR2:IC1.7
SRST2: CON:IC1.10, MOTOR3:C23.1, MOTOR3:IC1.7
SRST3: CON:IC1.12, MOTOR4:C23.1, MOTOR4:IC1.7
SRST4: CON:IC1.3, DRIBBLER:C23.1, DRIBBLER:IC1.7
SRST5: CON:IC1.1, CON:IR.P$4
SWCLK: CON:X1.26, DEBUG:RN4.6
SWDIO: CON:X1.27, DEBUG:RN4.5, DEBUG:RN4.8
TX0: CON:X1.29, MOTOR1:RN6.8
TX1: CON:X1.8, MOTOR2:RN6.8
TX2: CON:X1.10, MOTOR3:RN6.8
TX3: CON:X1.20, MOTOR4:RN6.8
TX4: CON:X1.6, DRIBBLER:RN6.8
TX5: CON:IR.P$3, CON:X1.4
TX6: CON:X1.22, DEBUG:RN5.8
TX7: CON:EXT.P$5, CON:X1.25
USB-ATT: CON:X1.11, POWER:IC20.14
VCC: CON:EXT.P$1, CON:KD.P$12, DRIBBLER:C5.1, DRIBBLER:C6.1, DRIBBLER:C7.1, DRIBBLER:C8.1, DRIBBLER:C9.1, DRIBBLER:C10.1, DRIBBLER:C11.1, DRIBBLER:C13.1, DRIBBLER:C14.1, DRIBBLER:C22.1, DRIBBLER:C157.1, DRIBBLER:IC1.8, DRIBBLER:Q1.3, DRIBBLER:Q1.4, DRIBBLER:Q1.D1, DRIBBLER:Q2.3, DRIBBLER:Q2.4, DRIBBLER:Q2.D1, DRIBBLER:Q3.3, DRIBBLER:Q3.4, DRIBBLER:Q3.D1, DRIBBLER:R22.2, MOTOR1:C6.1, MOTOR1:C7.1, MOTOR1:C8.1, MOTOR1:C9.1, MOTOR1:C10.1, MOTOR1:C11.1, MOTOR1:C13.1, MOTOR1:C14.1, MOTOR1:C15.1, MOTOR1:C16.+, MOTOR1:C22.1, MOTOR1:C157.1, MOTOR1:IC1.8, MOTOR1:Q1.3, MOTOR1:Q1.4, MOTOR1:Q1.D1, MOTOR1:Q2.3, MOTOR1:Q2.4, MOTOR1:Q2.D1, MOTOR1:Q3.3, MOTOR1:Q3.4, MOTOR1:Q3.D1, MOTOR1:R22.2, MOTOR2:C6.1, MOTOR2:C7.1, MOTOR2:C8.1, MOTOR2:C9.1, MOTOR2:C10.1, MOTOR2:C11.1, MOTOR2:C13.1, MOTOR2:C14.1, MOTOR2:C15.1, MOTOR2:C16.+, MOTOR2:C22.1, MOTOR2:C157.1, MOTOR2:IC1.8, MOTOR2:Q1.3, MOTOR2:Q1.4, MOTOR2:Q1.D1, MOTOR2:Q2.3, MOTOR2:Q2.4, MOTOR2:Q2.D1, MOTOR2:Q3.3, MOTOR2:Q3.4, MOTOR2:Q3.D1, MOTOR2:R22.2, MOTOR3:C6.1, MOTOR3:C7.1, MOTOR3:C8.1, MOTOR3:C9.1, MOTOR3:C10.1, MOTOR3:C11.1, MOTOR3:C13.1, MOTOR3:C14.1, MOTOR3:C15.1, MOTOR3:C16.+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
